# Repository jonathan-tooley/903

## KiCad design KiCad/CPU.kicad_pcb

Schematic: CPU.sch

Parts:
C1, C2, C3, C4, C5, C6, C7: 100n; C_Rect_L7.0mm_W2.5mm_P5.00mm
C8: 10u; CP_Radial_D5.0mm_P2.50mm
J1: DB9; DB9FC
P1.1: Control Panel; TerminalBlock_Pheonix_PT-3.5mm_4pol
P1.2: Display Unit; TerminalBlock_Pheonix_PT-3.5mm_4pol
P1.3: Tape Punch; TerminalBlock_Pheonix_PT-3.5mm_12pol
P1.4: Tape Reader; TerminalBlock_Pheonix_PT-3.5mm_12pol
P1.5: CONN_01X02; TerminalBlock_Pheonix_PT-3.5mm_2pol
P1.6: Plotter; TerminalBlock_Pheonix_PT-3.5mm_12pol
R1, R1.7, R1.8, R2, R3, R4, R5, R6: 10k; R5
U1.1: Raspberry_Pi_2_3; RASPI_BPLUS_MIRRORED
U1.2: PCA9516; DIP-16_W7.62mm
U1.3, U1.5: MCP23017; DIP-28_W7.62mm
U1.4: MAX232; DIP-16_W7.62mm

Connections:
0v: C4.1, C5.2, C6.2, C7.2, C8.2, J1.5, P1.1.4, P1.2.4, P1.3.12, P1.4.12, P1.5.2, P1.6.12, U1.1.20 (GND), U1.2.8, U1.2.9, U1.3.10 (GND), U1.4.15 (GND), U1.5.10 (GND), U1.5.15 (A0)
+3.3V: U1.1.1 (3V3), U1.2.16
+5v: C3.1, C5.1, C6.1, C7.1, C8.1, P1.1.1, P1.2.1, P1.3.11, P1.4.11, P1.5.1, P1.6.11, R1.1, R1.7.1, R1.8.1, R2.1, R3.1, R4.1, R5.2, R6.2, U1.1.2 (5V), U1.1.4 (5V), U1.3.9 (VCC), U1.3.15 (A0), U1.3.16 (A1), U1.3.17 (A2), U1.3.18 (~RESET), U1.4.16 (VCC), U1.5.9 (VCC), U1.5.16 (A1), U1.5.17 (A2), U1.5.18 (~RESET)
/Black: P1.3.8, U1.3.21 (GPA0)
/Blue: P1.3.4, U1.3.25 (GPA4)
/Grey: P1.3.7, U1.3.22 (GPA1)
/Mauve: P1.3.6, U1.3.23 (GPA2)
/Orange: P1.3.5, U1.3.24 (GPA3)
/Red: P1.3.1, U1.3.28 (GPA7)
/White: P1.3.3, U1.3.26 (GPA5)
/Yellow: P1.3.2, U1.3.27 (GPA6)
DisplayEnable: U1.1.12 (GPIO18_(GEN1)), U1.2.15
IOEnable: U1.1.13 (GPIO27_(GEN2)), U1.2.12
unnamed: C1.1, U1.4.1 (C1+)
unnamed: C1.2, U1.4.3 (C1-)
unnamed: C2.1, U1.4.4 (C2+)
unnamed: C2.2, U1.4.5 (C2-)
unnamed: C3.2, J1.4, U1.4.2 (VS+)
unnamed: C4.2, J1.7, U1.4.6 (VS-)
unnamed: J1.2, U1.4.14 (T1OUT)
unnamed: J1.3, U1.4.13 (R1IN)
unnamed: P1.1.2, R6.1, U1.2.3
unnamed: P1.1.3, R5.1, U1.2.4
unnamed: P1.2.2, R4.2, U1.2.13
unnamed: P1.2.3, R3.2, U1.2.14
unnamed: P1.4.1, U1.3.8 (GPB7)
unnamed: P1.4.2, U1.3.7 (GPB6)
unnamed: P1.4.3, U1.3.6 (GPB5)
unnamed: P1.4.4, U1.3.5 (GPB4)
unnamed: P1.4.5, U1.3.4 (GPB3)
unnamed: P1.4.6, U1.3.3 (GPB2)
unnamed: P1.4.7, U1.3.2 (GPB1)
unnamed: P1.4.8, U1.3.1 (GPB0)
unnamed: P1.6.1, U1.5.28 (GPA7)
unnamed: P1.6.2, U1.5.27 (GPA6)
unnamed: P1.6.3, U1.5.26 (GPA5)
unnamed: P1.6.4, U1.5.25 (GPA4)
unnamed: P1.6.5, U1.5.24 (GPA3)
unnamed: P1.6.6, U1.5.23 (GPA2)
unnamed: P1.6.7, U1.5.22 (GPA1)
unnamed: P1.6.8, U1.5.21 (GPA0)
unnamed: R1.7.2, U1.2.7
unnamed: R1.8.2, U1.2.6
unnamed: U1.1.3 ((SDA1)_GPIO2), U1.2.2
unnamed: U1.1.5 ((SCL1)_GPIO3), U1.2.1
unnamed: U1.1.8 ((TXD0)_GPIO14), U1.4.11 (T1IN)
unnamed: U1.1.10 ((RXD0)_GPIO15), U1.4.12 (R1OUT)
PanelEnable: U1.1.11 (GPIO17_(GEN0)), U1.2.5
PlotterA: P1.6.9, U1.1.38 (GPIO20)
PlotterB: P1.6.10, U1.1.40 (GPIO21)
PunchA: P1.3.9, U1.1.15 (GPIO22_(GEN3))
PunchB: P1.3.10, U1.1.16 (GPIO23_(GEN4))
ReaderA: P1.4.9, U1.1.18 (GPIO24_(GEN5))
ReaderB: P1.4.10, U1.1.22 (GPIO25_(GEN6))
SCL: R2.2, U1.2.10, U1.3.12 (SCL), U1.5.12 (SCL)
SDA: R1.2, U1.2.11, U1.3.13 (SDA), U1.5.13 (SDA)

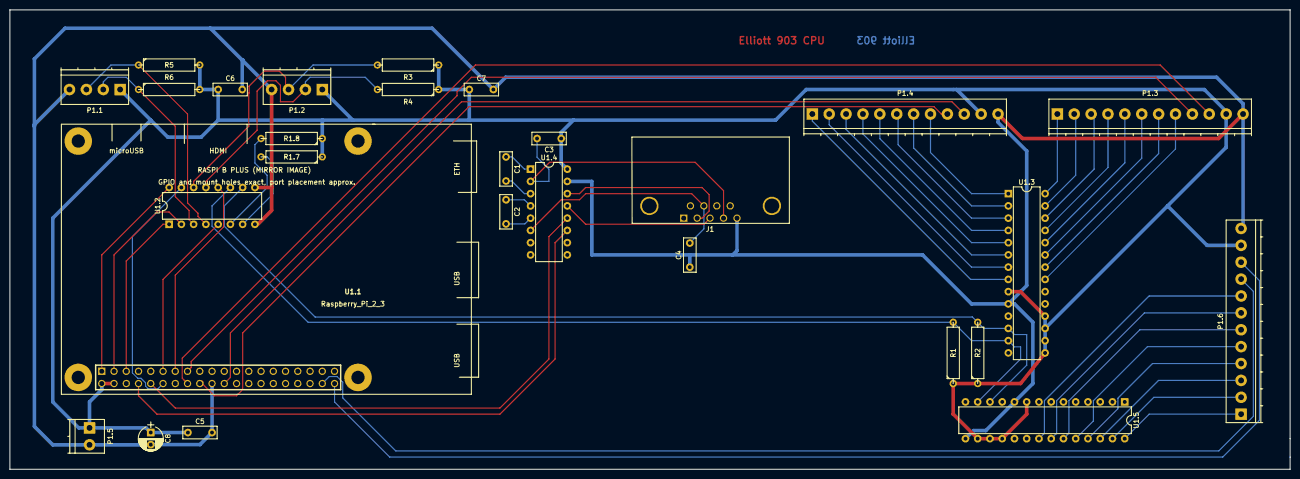
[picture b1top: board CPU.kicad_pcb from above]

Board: 2 copper layers, 265.4 x 95.2 mm, 28 parts (0 on the bottom side), 56 nets.

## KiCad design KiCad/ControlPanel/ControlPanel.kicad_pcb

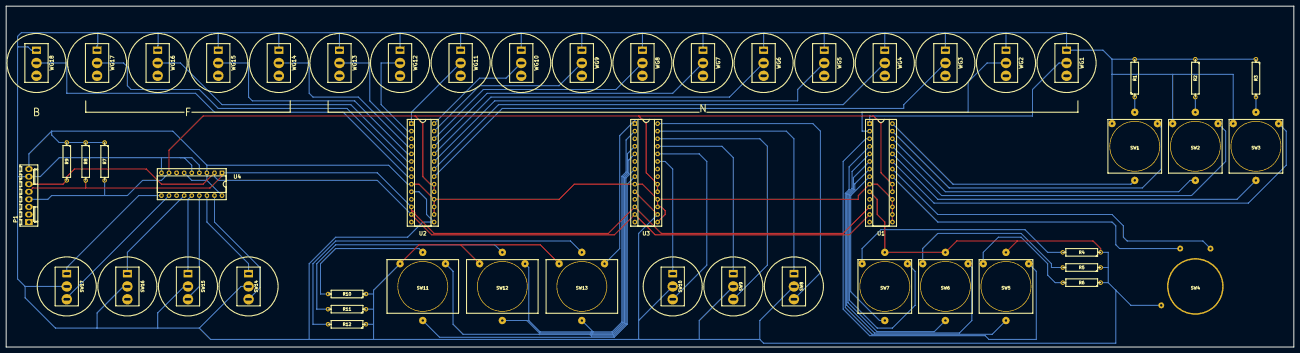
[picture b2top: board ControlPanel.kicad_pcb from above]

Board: 2 copper layers, 431.8 x 114.3 mm, 52 parts (0 on the bottom side), 51 nets.

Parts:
P1: CONN_01X08; Molex_KK-6410-08_08x2.54mm_Straight
R1, R2, R3, R4, R5, R6, R10, R11, R12: 330R; R5
R7, R8, R9: 10k; R5
SW1: Reset; EAO31
SW2: On; EAO31
SW3: Off; EAO31
SW4: Key Switch; C&K_Keyswitch
SW5: Jump; EAO31
SW6: Stop; EAO31
SW7: Restart; EAO31
SW8: Trace 3; SW_SPST_Toggle
SW9: Trace 2; SW_SPST_Toggle
SW10: Trace 1; SW_SPST_Toggle
SW11: Interrupt 1; EAO31_Rect
SW12: Interrupt 2; EAO31_Rect
SW13: Interrupt 3; EAO31_Rect
SW14: Obey; SW_SPST_Toggle
SW15: Enter; SW_SPST_Toggle
SW16: Cycle Repeat; SW_SPST_Toggle
SW17: Cycle / Order Stop; SW_SPST_Toggle
U1, U2, U3: MCP23017; DIP-28_W7.62mm_Socket
U4: MCP23008; DIP-18_W7.62mm_Socket
WG1, WG14: 1; SW_SPST_Toggle
WG2, WG15: 2; SW_SPST_Toggle
WG3, WG16: 4; SW_SPST_Toggle
WG4, WG17: 8; SW_SPST_Toggle
WG5: 16; SW_SPST_Toggle
WG6: 32; SW_SPST_Toggle
WG7: 64; SW_SPST_Toggle
WG8: 128; SW_SPST_Toggle
WG9: 256; SW_SPST_Toggle
WG10: 512; SW_SPST_Toggle
WG11: 1024; SW_SPST_Toggle
WG12: 2048; SW_SPST_Toggle
WG13: 4096; SW_SPST_Toggle
WG18: /; SW_SPST_Toggle

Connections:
0V: P1.7, R1.2, R2.1, R3.1, R4.1, R5.1, R6.1, R10.1, R11.1, R12.1, SW1.1, SW2.1, SW3.1, SW4.1, SW5.3, SW6.3, SW7.3, SW8.1, SW9.1, SW10.1, SW11.1, SW12.1, SW13.1, SW14.1, SW15.1, SW16.1, SW17.1, U1.10, U2.10, U2.15, U3.10, U3.16, U4.4, U4.5, U4.9, WG1.2, WG2.2, WG3.2, WG4.2, WG5.2, WG6.2, WG7.2, WG8.2, WG9.2, WG10.2, WG11.2, WG12.2, WG13.2, WG14.2, WG15.2, WG16.2, WG17.2, WG18.2
+5V: P1.8, R7.1, R8.1, R9.1, U1.9, U1.15, U1.16, U1.17, U1.18, U2.9, U2.16, U2.17, U2.18, U3.9, U3.15, U3.17, U3.18, U4.3, U4.6, U4.18
unnamed: R1.1, SW1.3
unnamed: R2.2, SW2.3
unnamed: R3.2, SW3.3
unnamed: R4.2, SW7.1
unnamed: R5.2, SW6.1
unnamed: R6.2, SW5.1
unnamed: R7.2, U1.19, U1.20, U2.19, U2.20, U3.19, U3.20, U4.8
unnamed: R8.2, U1.12, U2.12, U3.12, U4.1
unnamed: R9.2, U1.13, U2.13, U3.13, U4.2
unnamed: R10.2, SW11.3
unnamed: R11.2, SW12.3
unnamed: R12.2, SW13.3
unnamed: SW1.2, U1.27
unnamed: SW1.4, U1.28
unnamed: SW2.2, U1.25
unnamed: SW2.4, U1.26
unnamed: SW3.2, U1.23
unnamed: SW3.4, U1.24
unnamed: SW5.2, U1.3
unnamed: SW5.4, U1.4
unnamed: SW6.2, U1.5
unnamed: SW6.4, U1.6
unnamed: SW7.2, U1.7
unnamed: SW7.4, U1.8
unnamed: SW11.2, U3.7
unnamed: SW11.4, U3.8
unnamed: SW12.2, U3.4
unnamed: SW12.4, U3.5
unnamed: SW13.2, U3.1
unnamed: SW13.4, U3.2
unnamed: SW16.2, U4.13
unnamed: U1.1, WG1.1
unnamed: U1.2, WG2.1
unnamed: U2.1, WG11.1
unnamed: U2.2, WG12.1
unnamed: U2.3, WG13.1
unnamed: U2.4, WG14.1
unnamed: U2.5, WG15.1
unnamed: U2.6, WG16.1
unnamed: U2.7, WG17.1
unnamed: U2.8, WG18.1
unnamed: U2.21, WG3.1
unnamed: U2.22, WG4.1
unnamed: U2.23, WG5.1
unnamed: U2.24, WG6.1
unnamed: U2.25, WG7.1
unnamed: U2.26, WG8.1
unnamed: U2.27, WG9.1
unnamed: U2.28, WG10.1

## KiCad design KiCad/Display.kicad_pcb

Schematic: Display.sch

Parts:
C1, C2, C3, C4: LED; LED_D5.0mm
DA1, DA2, DA3, DA4, DA5, DA6, DA7, DA8, DA9, DA10, DA11, DA12, DA13, DA14, DA15, DA16, DA17, DA18: LED; LED_D5.0mm
DB1, DB2, DB3, DB4, DB5, DB6, DB7, DB8, DB9, DB10, DB11, DB12, DB13, DB14, DB15, DB16, DB17, DB18: LED; LED_D5.0mm
DQ1, DQ2, DQ3, DQ4, DQ5, DQ6, DQ7, DQ8, DQ9, DQ10, DQ11, DQ12, DQ13, DQ14, DQ15, DQ16, DQ17, DQ18: LED; LED_D5.0mm
DS1, DS2, DS3, DS4, DS5, DS6, DS7, DS8, DS9, DS10, DS11, DS12, DS13, DS14, DS15, DS16, DS17, DS18: LED; LED_D5.0mm
I1, I2, I3, I4: LED; LED_D5.0mm
J1: CONN_01X04; Pin_Header_Angled_1x04_Pitch2.54mm
R1, R2, R3, R4, R5, R6, R7, R8, R9, R10: 470R; TerminalBlock_Pheonix_MPT-2.54mm_9pol
U1, U2, U3, U4, U6: MCP23017; Mirror-DIP-28_W7.62mm

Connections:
0v: J1.4, R1.1, R2.1, R3.1, R4.1, R5.1, R6.1, R7.1, R8.1, R9.1, R10.1, U1.10 (GND), U2.10 (GND), U2.15 (A0), U3.10 (GND), U3.15 (A0), U3.16 (A1), U4.10 (GND), U4.17 (A2), U6.10 (GND), U6.16 (A1)
+5v: J1.1, U1.9 (VCC), U1.15 (A0), U1.16 (A1), U1.17 (A2), U1.18 (~RESET), U2.9 (VCC), U2.16 (A1), U2.17 (A2), U2.18 (~RESET), U3.9 (VCC), U3.17 (A2), U3.18 (~RESET), U4.9 (VCC), U4.15 (A0), U4.16 (A1), U4.18 (~RESET), U6.9 (VCC), U6.15 (A0), U6.17 (A2), U6.18 (~RESET)
unnamed: C1.1 (K), R10.8
unnamed: C1.2 (A), U6.22 (GPA1)
unnamed: C2.1 (K), R10.6
unnamed: C2.2 (A), U6.24 (GPA3)
unnamed: C3.1 (K), R10.4
unnamed: C3.2 (A), U6.26 (GPA5)
unnamed: C4.1 (K), R10.2
unnamed: C4.2 (A), U6.28 (GPA7)
unnamed: DA1.1 (K), R1.9
unnamed: DA1.2 (A), U1.1 (GPB0)
unnamed: DA2.1 (K), R1.8
unnamed: DA2.2 (A), U1.2 (GPB1)
unnamed: DA3.1 (K), R1.7
unnamed: DA3.2 (A), U1.3 (GPB2)
unnamed: DA4.1 (K), R1.6
unnamed: DA4.2 (A), U1.4 (GPB3)
unnamed: DA5.1 (K), R1.5
unnamed: DA5.2 (A), U1.5 (GPB4)
unnamed: DA6.1 (K), R1.4
unnamed: DA6.2 (A), U1.6 (GPB5)
unnamed: DA7.1 (K), R1.3
unnamed: DA7.2 (A), U1.7 (GPB6)
unnamed: DA8.1 (K), R1.2
unnamed: DA8.2 (A), U1.8 (GPB7)
unnamed: DA9.1 (K), R2.9
unnamed: DA9.2 (A), U1.21 (GPA0)
unnamed: DA10.1 (K), R2.8
unnamed: DA10.2 (A), U1.22 (GPA1)
unnamed: DA11.1 (K), R2.7
unnamed: DA11.2 (A), U1.23 (GPA2)
unnamed: DA12.1 (K), R2.6
unnamed: DA12.2 (A), U1.24 (GPA3)
unnamed: DA13.1 (K), R2.5
unnamed: DA13.2 (A), U1.25 (GPA4)
unnamed: DA14.1 (K), R2.4
unnamed: DA14.2 (A), U1.26 (GPA5)
unnamed: DA15.1 (K), R2.3
unnamed: DA15.2 (A), U1.27 (GPA6)
unnamed: DA16.1 (K), R2.2
unnamed: DA16.2 (A), U1.28 (GPA7)
unnamed: DA17.1 (K), R9.9
unnamed: DA17.2 (A), U6.1 (GPB0)
unnamed: DA18.1 (K), R9.8
unnamed: DA18.2 (A), U6.2 (GPB1)
unnamed: DB1.1 (K), R3.9
unnamed: DB1.2 (A), U2.1 (GPB0)
unnamed: DB2.1 (K), R3.8
unnamed: DB2.2 (A), U2.2 (GPB1)
unnamed: DB3.1 (K), R3.7
unnamed: DB3.2 (A), U2.3 (GPB2)
unnamed: DB4.1 (K), R3.6
unnamed: DB4.2 (A), U2.4 (GPB3)
unnamed: DB5.1 (K), R3.5
unnamed: DB5.2 (A), U2.5 (GPB4)
unnamed: DB6.1 (K), R3.4
unnamed: DB6.2 (A), U2.6 (GPB5)
unnamed: DB7.1 (K), R3.3
unnamed: DB7.2 (A), U2.7 (GPB6)
unnamed: DB8.1 (K), R3.2
unnamed: DB8.2 (A), U2.8 (GPB7)
unnamed: DB9.1 (K), R4.9
unnamed: DB9.2 (A), U2.21 (GPA0)
unnamed: DB10.1 (K), R4.8
unnamed: DB10.2 (A), U2.22 (GPA1)
unnamed: DB11.1 (K), R4.7
unnamed: DB11.2 (A), U2.23 (GPA2)
unnamed: DB12.1 (K), R4.6
unnamed: DB12.2 (A), U2.24 (GPA3)
unnamed: DB13.1 (K), R4.5
unnamed: DB13.2 (A), U2.25 (GPA4)
unnamed: DB14.1 (K), R4.4
unnamed: DB14.2 (A), U2.26 (GPA5)
unnamed: DB15.1 (K), R4.3
unnamed: DB15.2 (A), U2.27 (GPA6)
unnamed: DB16.1 (K), R4.2
unnamed: DB16.2 (A), U2.28 (GPA7)
unnamed: DB17.1 (K), R9.7
unnamed: DB17.2 (A), U6.3 (GPB2)
unnamed: DB18.1 (K), R9.6
unnamed: DB18.2 (A), U6.4 (GPB3)
unnamed: DQ1.1 (K), R5.9
unnamed: DQ1.2 (A), U3.1 (GPB0)
unnamed: DQ2.1 (K), R5.8
unnamed: DQ2.2 (A), U3.2 (GPB1)
unnamed: DQ3.1 (K), R5.7
unnamed: DQ3.2 (A), U3.3 (GPB2)
unnamed: DQ4.1 (K), R5.6
unnamed: DQ4.2 (A), U3.4 (GPB3)
unnamed: DQ5.1 (K), R5.5
unnamed: DQ5.2 (A), U3.5 (GPB4)
unnamed: DQ6.1 (K), R5.4
unnamed: DQ6.2 (A), U3.6 (GPB5)
unnamed: DQ7.1 (K), R5.3
unnamed: DQ7.2 (A), U3.7 (GPB6)
unnamed: DQ8.1 (K), R5.2
unnamed: DQ8.2 (A), U3.8 (GPB7)
unnamed: DQ9.1 (K), R6.9
unnamed: DQ9.2 (A), U3.21 (GPA0)
unnamed: DQ10.1 (K), R6.8
unnamed: DQ10.2 (A), U3.22 (GPA1)
unnamed: DQ11.1 (K), R6.7
unnamed: DQ11.2 (A), U3.23 (GPA2)
unnamed: DQ12.1 (K), R6.6
unnamed: DQ12.2 (A), U3.24 (GPA3)
unnamed: DQ13.1 (K), R6.5
unnamed: DQ13.2 (A), U3.25 (GPA4)
unnamed: DQ14.1 (K), R6.4
unnamed: DQ14.2 (A), U3.26 (GPA5)
unnamed: DQ15.1 (K), R6.3
unnamed: DQ15.2 (A), U3.27 (GPA6)
unnamed: DQ16.1 (K), R6.2
unnamed: DQ16.2 (A), U3.28 (GPA7)
unnamed: DQ17.1 (K), R9.5
unnamed: DQ17.2 (A), U6.5 (GPB4)
unnamed: DQ18.1 (K), R9.4
unnamed: DQ18.2 (A), U6.6 (GPB5)
unnamed: DS1.1 (K), R7.9
unnamed: DS1.2 (A), U4.1 (GPB0)
unnamed: DS2.1 (K), R7.8
unnamed: DS2.2 (A), U4.2 (GPB1)
unnamed: DS3.1 (K), R7.7
unnamed: DS3.2 (A), U4.3 (GPB2)
unnamed: DS4.1 (K), R7.6
unnamed: DS4.2 (A), U4.4 (GPB3)
unnamed: DS5.1 (K), R7.5
unnamed: DS5.2 (A), U4.5 (GPB4)
unnamed: DS6.1 (K), R7.4
unnamed: DS6.2 (A), U4.6 (GPB5)
unnamed: DS7.1 (K), R7.3
unnamed: DS7.2 (A), U4.7 (GPB6)
unnamed: DS8.1 (K), R7.2
unnamed: DS8.2 (A), U4.8 (GPB7)
unnamed: DS9.1 (K), R8.9
unnamed: DS9.2 (A), U4.21 (GPA0)
unnamed: DS10.1 (K), R8.8
unnamed: DS10.2 (A), U4.22 (GPA1)
unnamed: DS11.1 (K), R8.7
unnamed: DS11.2 (A), U4.23 (GPA2)
unnamed: DS12.1 (K), R8.6
unnamed: DS12.2 (A), U4.24 (GPA3)
unnamed: DS13.1 (K), R8.5
unnamed: DS13.2 (A), U4.25 (GPA4)
unnamed: DS14.1 (K), R8.4
unnamed: DS14.2 (A), U4.26 (GPA5)
unnamed: DS15.1 (K), R8.3
unnamed: DS15.2 (A), U4.27 (GPA6)
unnamed: DS16.1 (K), R8.2
unnamed: DS16.2 (A), U4.28 (GPA7)
unnamed: DS17.1 (K), R9.3
unnamed: DS17.2 (A), U6.7 (GPB6)
unnamed: DS18.1 (K), R9.2
unnamed: DS18.2 (A), U6.8 (GPB7)
unnamed: I1.1 (K), R10.9
unnamed: I1.2 (A), U6.21 (GPA0)
unnamed: I2.1 (K), R10.7
unnamed: I2.2 (A), U6.23 (GPA2)
unnamed: I3.1 (K), R10.5
unnamed: I3.2 (A), U6.25 (GPA4)
unnamed: I4.1 (K), R10.3
unnamed: I4.2 (A), U6.27 (GPA6)
SCL: J1.3, U1.12 (SCL), U2.12 (SCL), U3.12 (SCL), U4.12 (SCL), U6.12 (SCL)
SDA: J1.2, U1.13 (SDA), U2.13 (SDA), U3.13 (SDA), U4.13 (SDA), U6.13 (SDA)

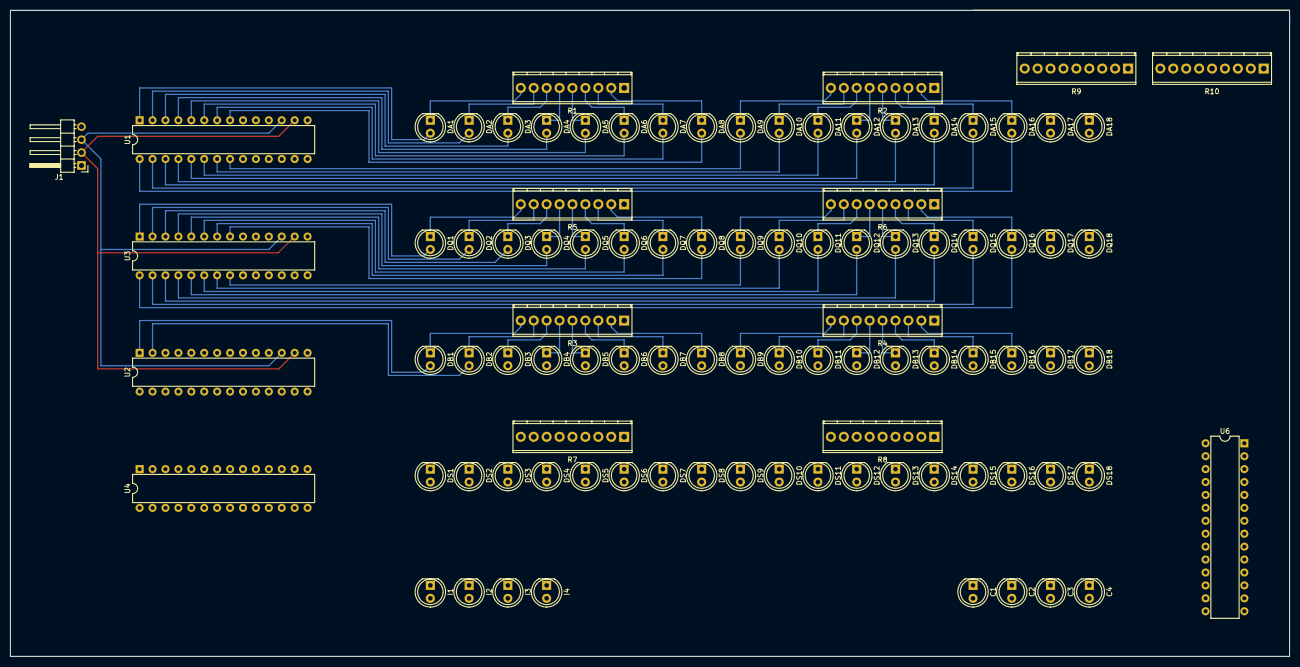
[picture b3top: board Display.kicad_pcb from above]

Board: 2 copper layers, 251.5 x 127.0 mm, 96 parts (0 on the bottom side), 164 nets.

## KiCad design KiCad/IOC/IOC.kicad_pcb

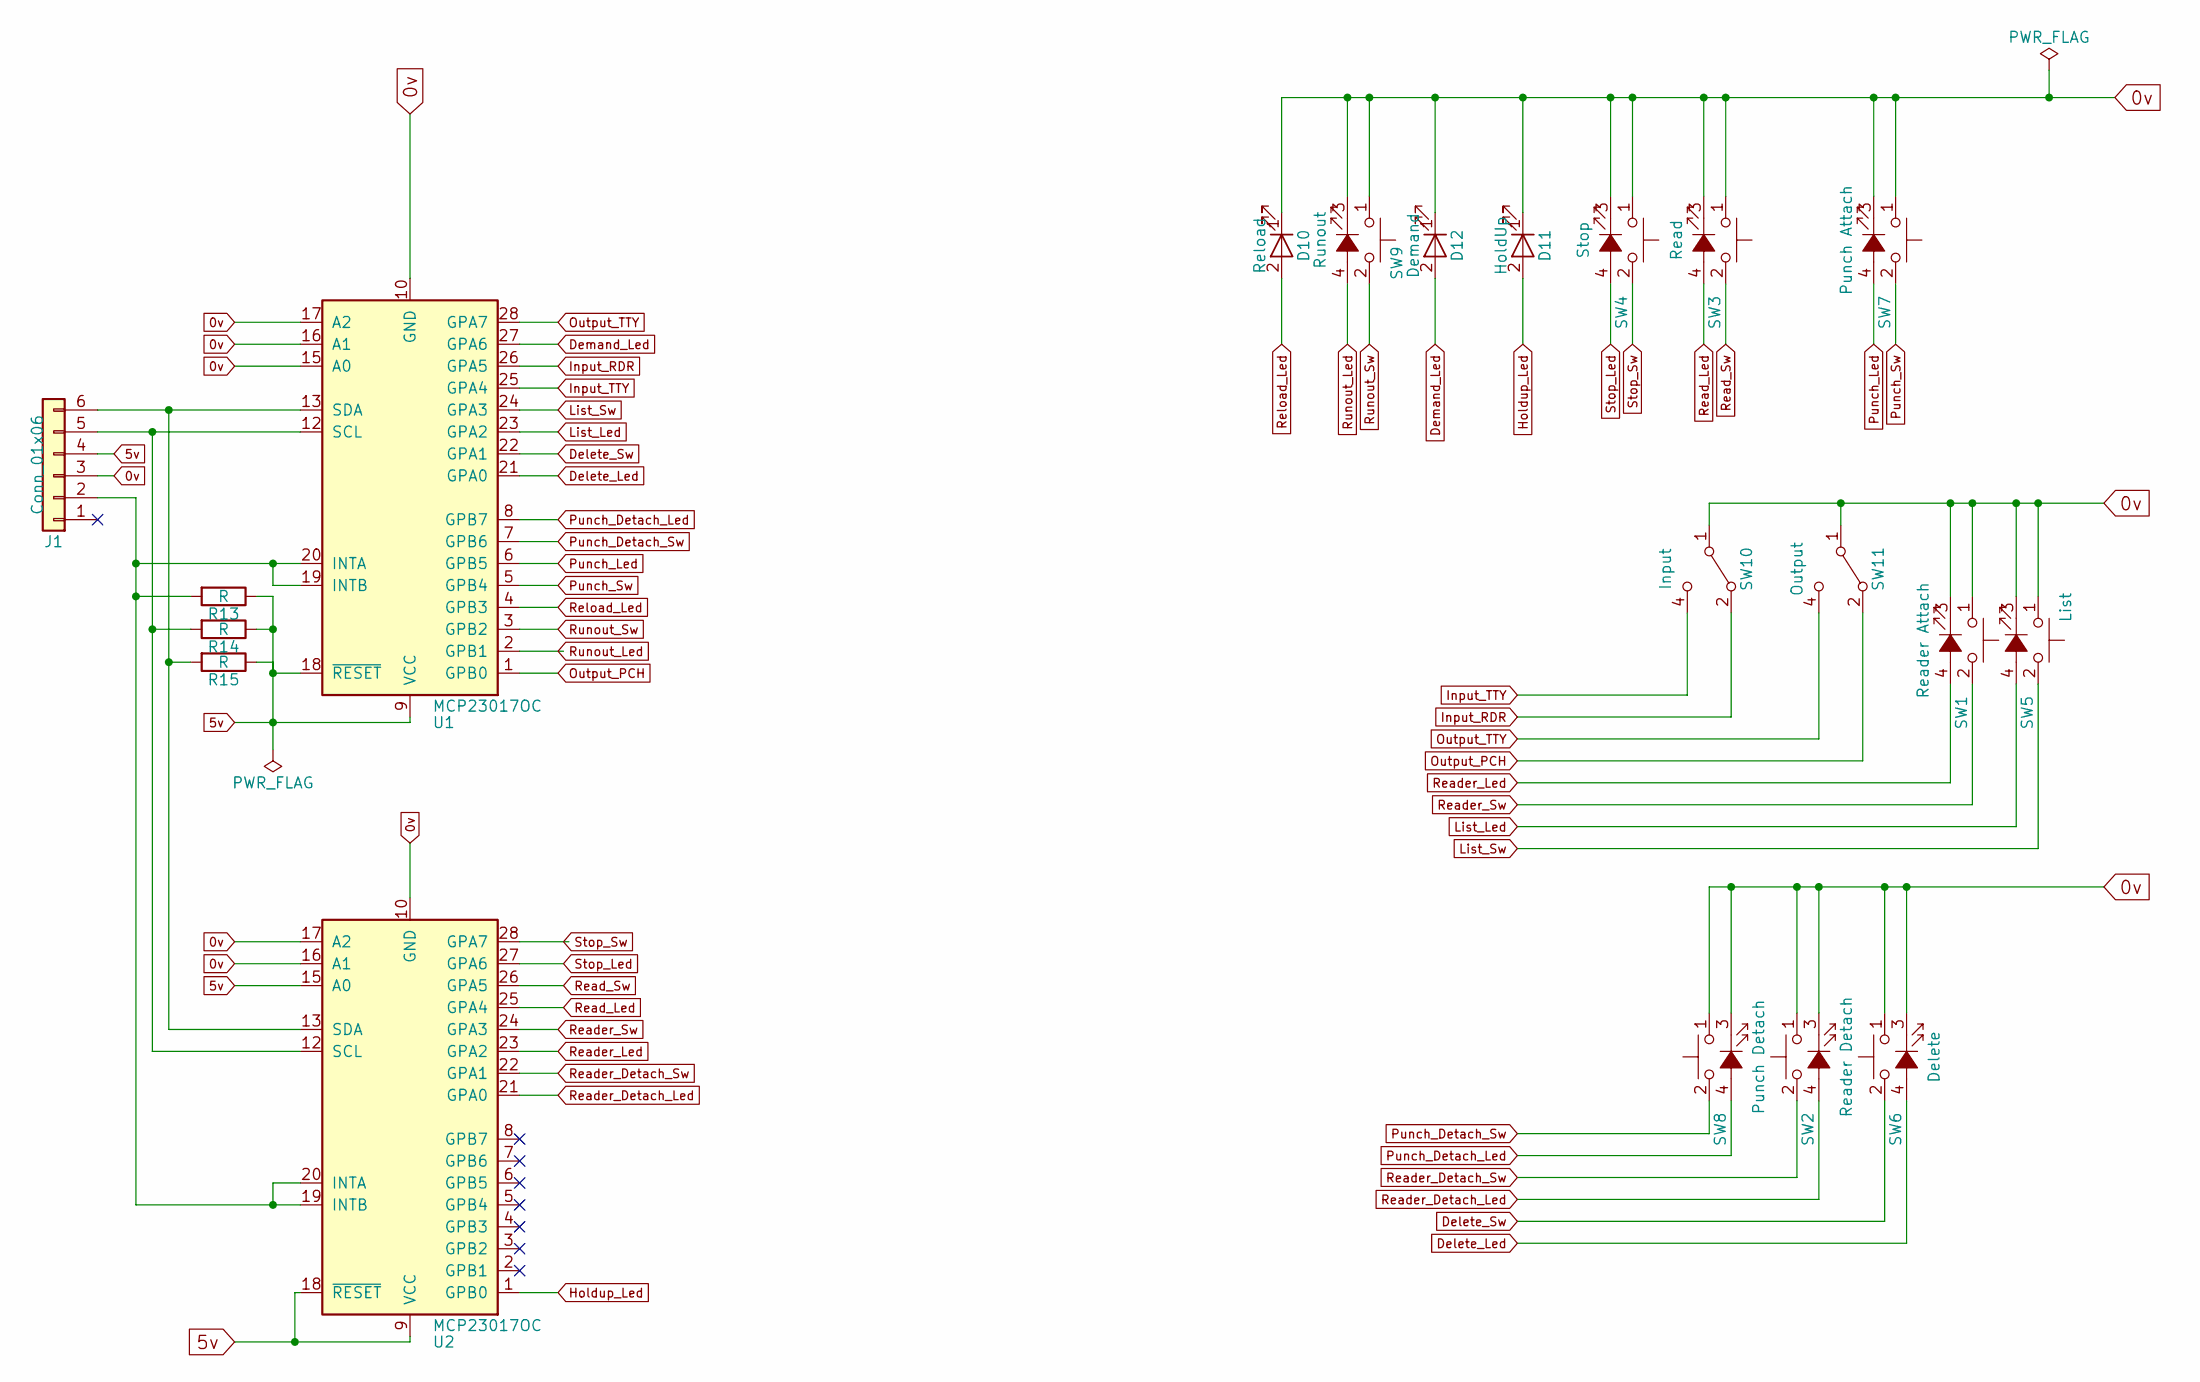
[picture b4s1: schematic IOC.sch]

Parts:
D10: Reload; EAO31_Led_Only
D11: HoldUp; EAO31_Led_Only
D12: Demand; EAO31_Led_Only
J1: Conn_01x06; Harwin_LTek-Male_06x2.00mm_Straight
R13, R14, R15: R; R5
SW1: Reader Attach; EAO31
SW2: Reader Detach; EAO31
SW3: Read; EAO31
SW4: Stop; EAO31
SW5: List; EAO31
SW6: Delete; EAO31
SW7: Punch Attach; EAO31
SW8: Punch Detach; EAO31
SW9: Runout; EAO31
SW10: Input; ALPSRotary
SW11: Output; ALPSRotary
U1, U2: MCP23017OC; DIP-28_W7.62mm_Socket_Mirror

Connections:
0v: D10.1 (K), D11.1 (K), D12.1 (K), J1.3, SW1.1, SW1.3 (K), SW2.1, SW2.3 (K), SW3.1, SW3.3 (K), SW4.1, SW4.3 (K), SW5.1, SW5.3 (K), SW6.1, SW6.3 (K), SW7.1, SW7.3 (K), SW8.1, SW8.3 (K), SW9.1, SW9.3 (K), SW10.1 (B), SW11.1 (B), U1.10 (GND), U1.15 (A0), U1.16 (A1), U1.17 (A2), U2.10 (GND), U2.16 (A1), U2.17 (A2)
5v: J1.4, R13.1, R14.1, R15.1, U1.9 (VCC), U1.18 (~RESET), U2.9 (VCC), U2.15 (A0), U2.18 (~RESET)
Delete_Led: SW6.4 (A), U1.21 (GPA0)
Delete_Sw: SW6.2, U1.22 (GPA1)
Demand_Led: D12.2 (A), U1.27 (GPA6)
Holdup_Led: D11.2 (A), U2.1 (GPB0)
Input_RDR: SW10.2 (A), U1.26 (GPA5)
Input_TTY: SW10.4 (C), U1.25 (GPA4)
List_Led: SW5.4 (A), U1.23 (GPA2)
List_Sw: SW5.2, U1.24 (GPA3)
unnamed: J1.2, R13.2, U1.19 (INTB), U1.20 (INTA), U2.19 (INTB), U2.20 (INTA)
unnamed: J1.5, R14.2, U1.12 (SCL), U2.12 (SCL)
unnamed: J1.6, R15.2, U1.13 (SDA), U2.13 (SDA)
Output_PCH: SW11.2 (A), U1.1 (GPB0)
Output_TTY: SW11.4 (C), U1.28 (GPA7)
Punch_Detach_Led: SW8.4 (A), U1.8 (GPB7)
Punch_Detach_Sw: SW8.2, U1.7 (GPB6)
Punch_Led: SW7.4 (A), U1.6 (GPB5)
Punch_Sw: SW7.2, U1.5 (GPB4)
Read_Led: SW3.4 (A), U2.25 (GPA4)
Read_Sw: SW3.2, U2.26 (GPA5)
Reader_Detach_Led: SW2.4 (A), U2.21 (GPA0)
Reader_Detach_Sw: SW2.2, U2.22 (GPA1)
Reader_Led: SW1.4 (A), U2.23 (GPA2)
Reader_Sw: SW1.2, U2.24 (GPA3)
Reload_Led: D10.2 (A), U1.4 (GPB3)
Runout_Led: SW9.4 (A), U1.2 (GPB1)
Runout_Sw: SW9.2, U1.3 (GPB2)
Stop_Led: SW4.4 (A), U2.27 (GPA6)
Stop_Sw: SW4.2, U2.28 (GPA7)

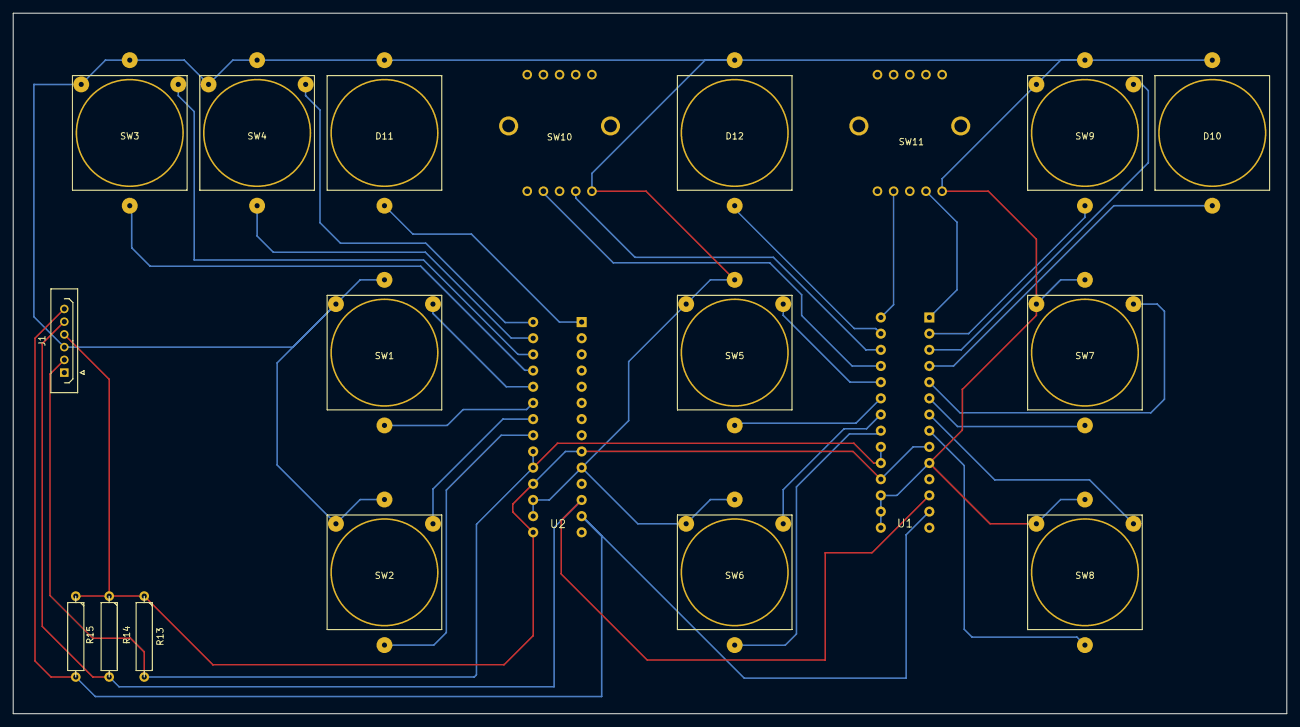
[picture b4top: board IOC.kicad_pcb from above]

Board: 2 copper layers, 200.0 x 110.0 mm, 20 parts (0 on the bottom side), 30 nets.

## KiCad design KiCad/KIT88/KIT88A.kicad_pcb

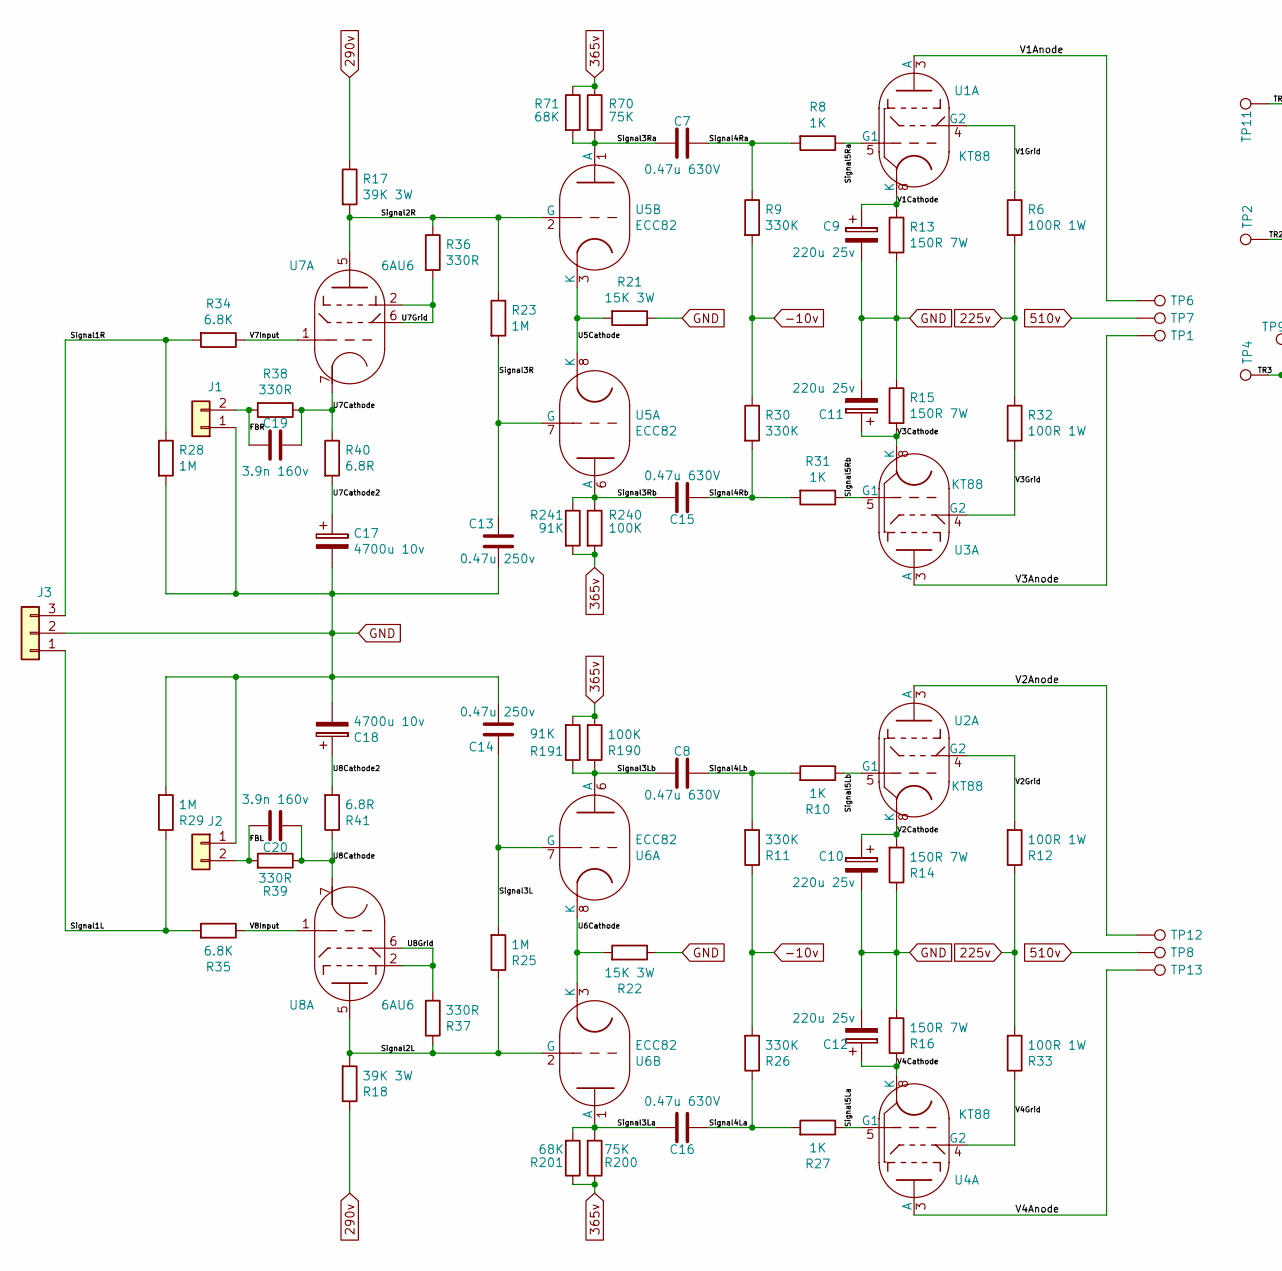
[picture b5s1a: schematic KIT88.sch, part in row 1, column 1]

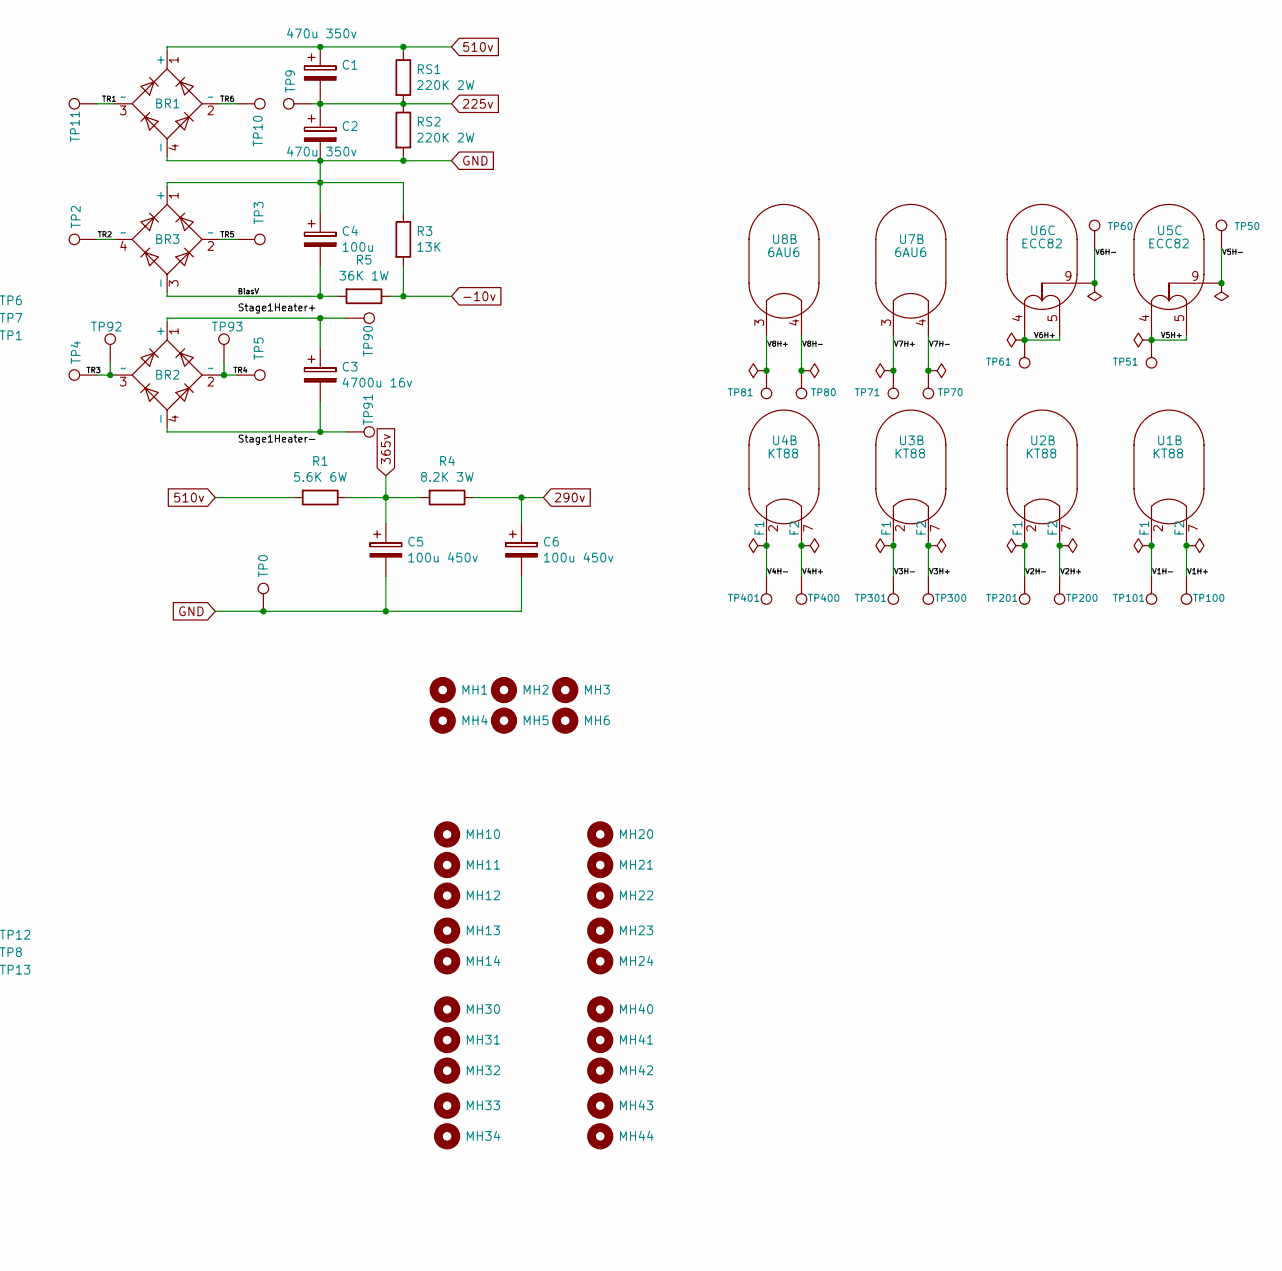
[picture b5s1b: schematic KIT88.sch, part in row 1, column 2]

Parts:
BR1: Diode_Bridge_32.0x5.6x17.0mm_P10.0mm_P7.5mm
BR2: Diode_Bridge_Vishay_GBL
BR3: Diode_Bridge_Round_D9.8mm
C1, C2: 470u 350v; CP_Radial_D35.0mm_P10.00mm_SnapIn
C3: 4700u 16v; CP_Radial_D17.0mm_P7.50mm
C4: 100u; CP_Radial_D10.0mm_P7.50mm
C5, C6: 100u 450v; CP_Radial_D25.0mm_P10.00mm_SnapIn
C7, C8, C15, C16: 0.47u 630V; C_Rect_L26.5mm_W11.5mm_P22.50mm_MKS4
C9, C10, C11, C12: 220u 25v; CP_Radial_D8.0mm_P3.80mm
C13, C14: 0.47u 250v; C_Rect_L18.0mm_W9.0mm_P15.00mm_FKS3_FKP3
C17, C18: 4700u 10v; CP_Radial_D17.0mm_P7.50mm
C19, C20: 3.9n 160v; C_Axial_L12.0mm_D6.5mm_P20.00mm_Horizontal
J1, J2: Molex_KK-396_A-41791-0002_1x02_P3.96mm_Vertical
J3: Molex_KK-396_A-41791-0003_1x03_P3.96mm_Vertical
MH1, MH2, MH3, MH4, MH5, MH6: MountingHole_3.2mm_M3
MH10, MH11, MH12, MH13, MH14, MH20, MH21, MH22, MH23, MH24, MH30, MH31, MH32, MH33, MH34, MH40, MH41, MH42, MH43, MH44: CoolingHole
R1: 5.6K 6W; R_Axial_Power_L20.0mm_W6.4mm_P30.48mm
R3: 13K; R_Axial_DIN0309_L9.0mm_D3.2mm_P15.24mm_Horizontal
R4: 8.2K 3W; R_Axial_DIN0414_L11.9mm_D4.5mm_P25.40mm_Horizontal
R5: 36K 1W; R_Axial_DIN0309_L9.0mm_D3.2mm_P15.24mm_Horizontal
R6, R12, R32, R33: 100R 1W; R_Axial_DIN0414_L11.9mm_D4.5mm_P20.32mm_Horizontal
R8, R10, R27, R31: 1K; R_Axial_DIN0309_L9.0mm_D3.2mm_P15.24mm_Horizontal
R9, R11, R26, R30: 330K; R_Axial_DIN0309_L9.0mm_D3.2mm_P15.24mm_Horizontal
R13, R14, R15, R16: 150R 7W; R_Axial_Power_L38.0mm_W6.4mm_P45.72mm
R17, R18: 39K 3W; R_Axial_DIN0414_L11.9mm_D4.5mm_P20.32mm_Horizontal
R21, R22: 15K 3W; R_Axial_DIN0414_L11.9mm_D4.5mm_P20.32mm_Horizontal
R23, R25, R28, R29: 1M; R_Axial_DIN0309_L9.0mm_D3.2mm_P15.24mm_Horizontal
R34, R35: 6.8K; R_Axial_DIN0309_L9.0mm_D3.2mm_P15.24mm_Horizontal
R36, R37, R38, R39: 330R; R_Axial_DIN0309_L9.0mm_D3.2mm_P15.24mm_Horizontal
R40, R41: 6.8R; R_Axial_DIN0309_L9.0mm_D3.2mm_P15.24mm_Horizontal
R70, R200: 75K; R_Axial_DIN0414_L11.9mm_D4.5mm_P20.32mm_Horizontal
R71, R201: 68K; R_Axial_DIN0414_L11.9mm_D4.5mm_P20.32mm_Horizontal
R190, R240: 100K; R_Axial_DIN0414_L11.9mm_D4.5mm_P20.32mm_Horizontal
R191, R241: 91K; R_Axial_DIN0414_L11.9mm_D4.5mm_P20.32mm_Horizontal
RS1, RS2: 220K 2W; R_Axial_DIN0414_L11.9mm_D4.5mm_P20.32mm_Horizontal
TP0: StarGround
TP1, TP2, TP3, TP4, TP5, TP6, TP7, TP8, TP9, TP10, TP11, TP12, TP13: TestPoint_Plated_Hole_D2.0mm
TP50, TP51, TP60, TP61, TP70, TP71, TP80, TP81, TP90, TP91, TP92, TP93, TP100, TP101, TP200, TP201, TP300, TP301, TP400, TP401: 2HolePad
U1, U2, U3, U4: KT88; Valve_Octal
U5, U6: ECC82; Valve_ECC-82
U7, U8: 6AU6; Valve_Mini_P

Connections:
225v: C1.2, C2.1, R6.2, R12.1, R32.1, R33.2, RS1.2, RS2.1, TP9.1
290v: C6.1, R4.1, R17.1, R18.1
365v: C5.1, R1.1, R4.2, R70.1, R71.1, R190.2, R191.2, R200.1, R201.1, R240.2, R241.2
510v: BR1.1 (+), C1.1, R1.2, RS1.1, TP7.1, TP8.1
-10v: R3.2, R5.1, R9.2, R11.1, R26.2, R30.1
/BiasV: BR3.3 (-), C4.2, R5.2
/FBL: C20.2, J2.2, R39.2
/FBR: C19.2, J1.2, R38.2
/Signal1L: J3.1, R29.1, R35.2
/Signal1R: J3.3, R28.1, R34.2
/Signal2L: R18.2, R25.1, R37.1, U6.2 (G), U8.5
/Signal2R: R17.2, R23.1, R36.1, U5.2 (G), U7.5
/Signal3L: C14.1, R25.2, U6.7 (G)
/Signal3La: C16.2, R200.2, R201.2, U6.1 (A)
/Signal3Lb: C8.2, R190.1, R191.1, U6.6 (A)
/Signal3R: C13.1, R23.2, U5.7 (G)
/Signal3Ra: C7.2, R70.2, R71.2, U5.1 (A)
/Signal3Rb: C15.2, R240.1, R241.1, U5.6 (A)
/Signal4La: C16.1, R26.1, R27.2
/Signal4Lb: C8.1, R10.2, R11.2
/Signal4Ra: C7.1, R8.2, R9.1
/Signal4Rb: C15.1, R30.2, R31.2
/Signal5La: R27.1, U4.5 (G1)
/Signal5Lb: R10.1, U2.5 (G1)
/Signal5Ra: R8.1, U1.5 (G1)
/Signal5Rb: R31.1, U3.5 (G1)
/TR1: BR1.3 (~~), TP11.1
/TR2: BR3.4 (~~), TP2.1
/TR3: BR2.3 (~~), TP4.1, TP92.1
/TR4: BR2.2 (~~), TP5.1, TP93.1
/TR5: BR3.2 (~~), TP3.1
/TR6: BR1.2 (~~), TP10.1
/U5Cathode: R21.2, U5.3 (K), U5.8 (K)
/U6Cathode: R22.2, U6.3 (K), U6.8 (K)
/U7Cathode: C19.1, R38.1, R40.1, U7.7
/U7Cathode2: C17.1, R40.2
/U7Grid: R36.2, U7.2, U7.6
/U8Cathode: C20.1, R39.1, R41.1, U8.7
/U8Cathode2: C18.1, R41.2
/U8Grid: R37.2, U8.2, U8.6
/V1Anode: TP6.1, U1.3 (A)
/V1Cathode: C9.1, R13.1, U1.8 (K)
/V1Grid: R6.1, U1.4 (G2)
/V1H+: TP100.1, U1.7 (F2)
/V1H-: TP101.1, U1.2 (F1)
/V2Anode: TP12.1, U2.3 (A)
/V2Cathode: C10.1, R14.2, U2.8 (K)
/V2Grid: R12.2, U2.4 (G2)
/V2H+: TP200.1, U2.7 (F2)
/V2H-: TP201.1, U2.2 (F1)
/V3Anode: TP1.1, U3.3 (A)
/V3Cathode: C11.1, R15.2, U3.8 (K)
/V3Grid: R32.2, U3.4 (G2)
/V3H+: TP300.1, U3.7 (F2)
/V3H-: TP301.1, U3.2 (F1)
/V4Anode: TP13.1, U4.3 (A)
/V4Cathode: C12.1, R16.1, U4.8 (K)
/V4Grid: R33.1, U4.4 (G2)
/V4H+: TP400.1, U4.7 (F2)
/V4H-: TP401.1, U4.2 (F1)
/V5H+: TP51.1, U5.4, U5.5
/V5H-: TP50.1, U5.9
/V6H+: TP61.1, U6.4, U6.5
/V6H-: TP60.1, U6.9
/V7H+: TP71.1, U7.3
/V7H-: TP70.1, U7.4
/V7Input: R34.1, U7.1
/V8H+: TP81.1, U8.3
/V8H-: TP80.1, U8.4
/V8Input: R35.1, U8.1
GND: BR1.4 (-), BR3.1 (+), C2.2, C4.1, C5.2, C6.2, C9.2, C10.2, C11.2, C12.2, C13.2, C14.2, C17.2, C18.2, J1.1, J2.1, J3.2, R3.1, R13.2, R14.1, R15.1, R16.2, R21.1, R22.1, R28.2, R29.2, RS2.2, TP0.1
unnamed: BR2.1 (+), C3.1, TP90.1
unnamed: BR2.4 (-), C3.2, TP91.1

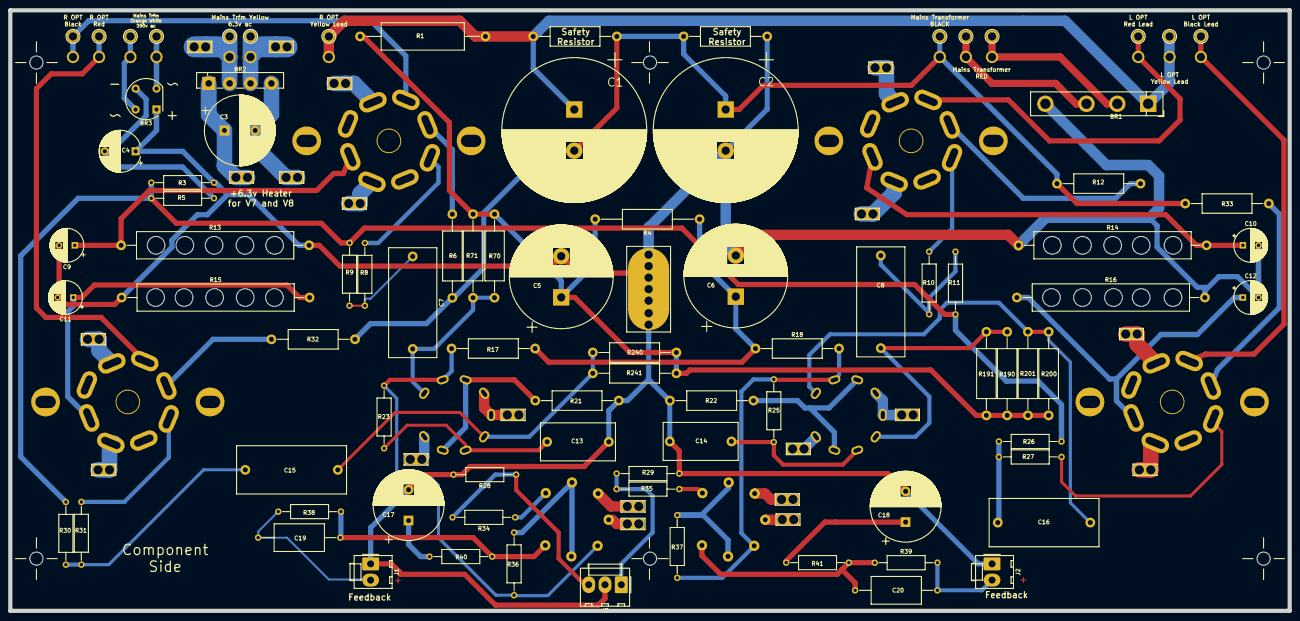
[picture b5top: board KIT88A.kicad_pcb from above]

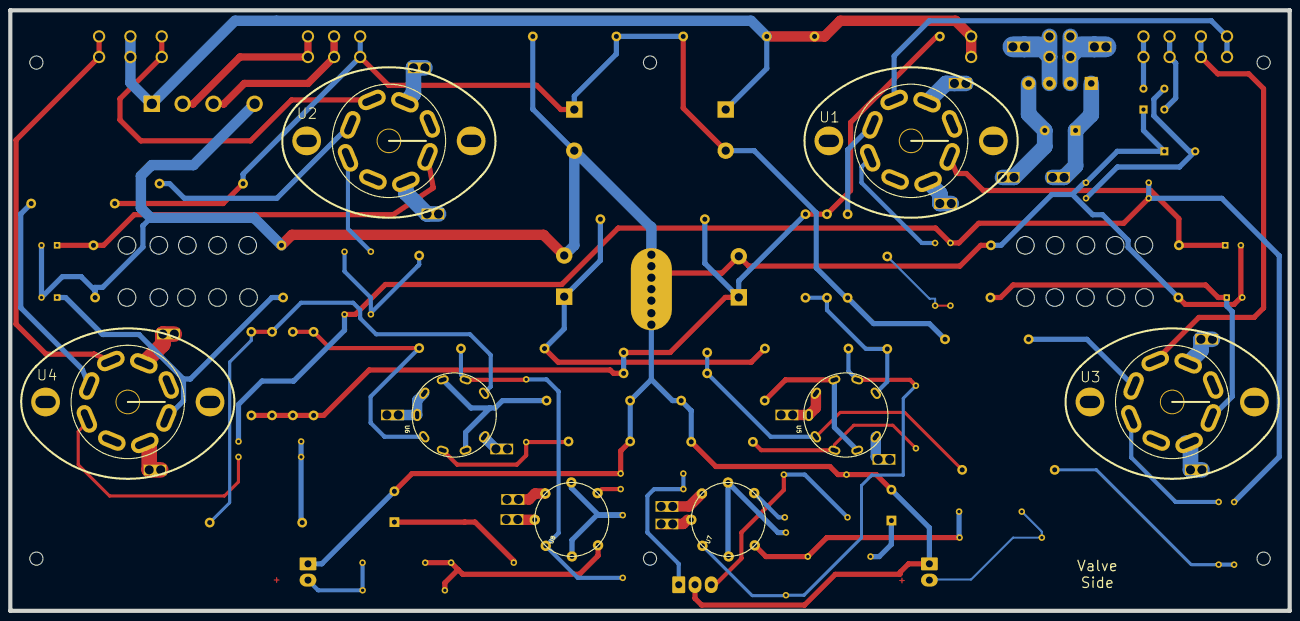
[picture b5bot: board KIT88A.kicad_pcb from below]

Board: 2 copper layers, 311.1 x 146.1 mm, 140 parts (8 on the bottom side), 73 nets.
